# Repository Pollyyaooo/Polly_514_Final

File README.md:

# EmoTrace
#### MSTI TECHIN 514 Final Project           
#### 01/06/2026-03/06/2026

## Project Overview

This project investigates emotion sensing as a process of externalization rather than interpretation.
It measures physiological arousal through galvanic skin response (GSR) and expresses it using a
stepper-motor-driven physical needle display.

Instead of identifying discrete emotions or presenting numerical readouts, the system focuses on
how affective states unfold over time. Changes in arousal are rendered as continuous physical
motion, allowing inertia, gradual transitions, and recovery to remain visible rather than being
collapsed into instantaneous values.

The project is composed of two physically separated devices: a sensing device and a display device,
connected wirelessly via BLE. The sensing device captures and processes physiological signals, while
the display device externalizes these signals as a slow, glanceable, and non-intrusive physical
artifact. Through this separation, the project explores how emotional states can be felt,
noticed, and reflected upon, without being classified or explained away.

## System Architecture

**Sensing Device**
- Captures electrodermal activity via finger electrodes and a GSR sensor module
- Performs basic digital signal processing (filtering, baseline normalization)
- Transmits a continuous arousal indicator via BLE

**Display Device**
- Receives arousal data wirelessly
- Drives a stepper-motor-based gauge needle as the primary expressive output
- Provides minimal user input and status indication
- Is implemented on a custom-designed PCB

## Battery Estimation

### Display Device
Spreadsheet link:  
https://1drv.ms/x/c/3520740a59bca320/IQBtffllcoQcSJlxG03brPWNAZ11j2MDRlCTxOjXR5vgqAk?e=tpQcXu

### Sensing Device
Spreadsheet link:  
https://1drv.ms/x/c/3520740a59bca320/IQDMDjtJkVfMQYsOUzpoie-YAZGBVunHImL63yKkG8l4-dY?e=yHCJq8

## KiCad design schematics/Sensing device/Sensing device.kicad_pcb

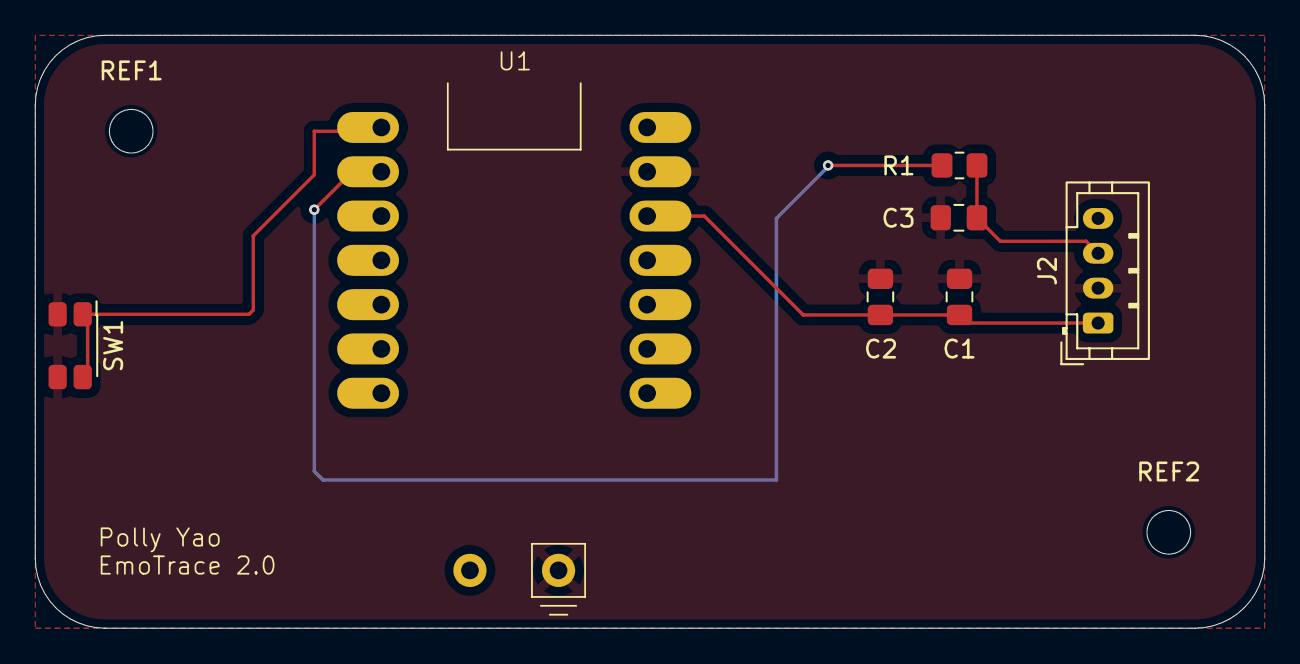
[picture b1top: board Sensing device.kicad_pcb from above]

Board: 2 copper layers, 70.5 x 34.0 mm, 9 parts (0 on the bottom side), 5 nets.

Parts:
C1: 10uF; C_0805_2012Metric_Pad1.18x1.45mm_HandSolder
C2, C3: 0.1uF; C_0805_2012Metric_Pad1.18x1.45mm_HandSolder
J2: Grove_GSR; JST_PH_B4B-PH-K_1x04_P2.00mm_Vertical
R1: 220Ω; R_0805_2012Metric_Pad1.20x1.40mm_HandSolder
REF1, REF2: MountingHole_2.5mm
SW1: SW_Push; SW_SPST_EVQP7A
U1: XIAO ESP32C3; XIAO_ESP32

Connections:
+3V3: C1.1, C2.1, J2.1, U1.12 (3V3)
/CAL_BTN: SW1.1, U1.1 (GPIO1_A0_D0)
/GSR_SIG: R1.2, U1.2 (GPIO2_A1_D1)
GND: C1.2, C2.2, C3.1, J2.2, SW1.2, U1.13 (GND), U1.16 (-BATT)
unnamed: C3.2, J2.3, R1.1

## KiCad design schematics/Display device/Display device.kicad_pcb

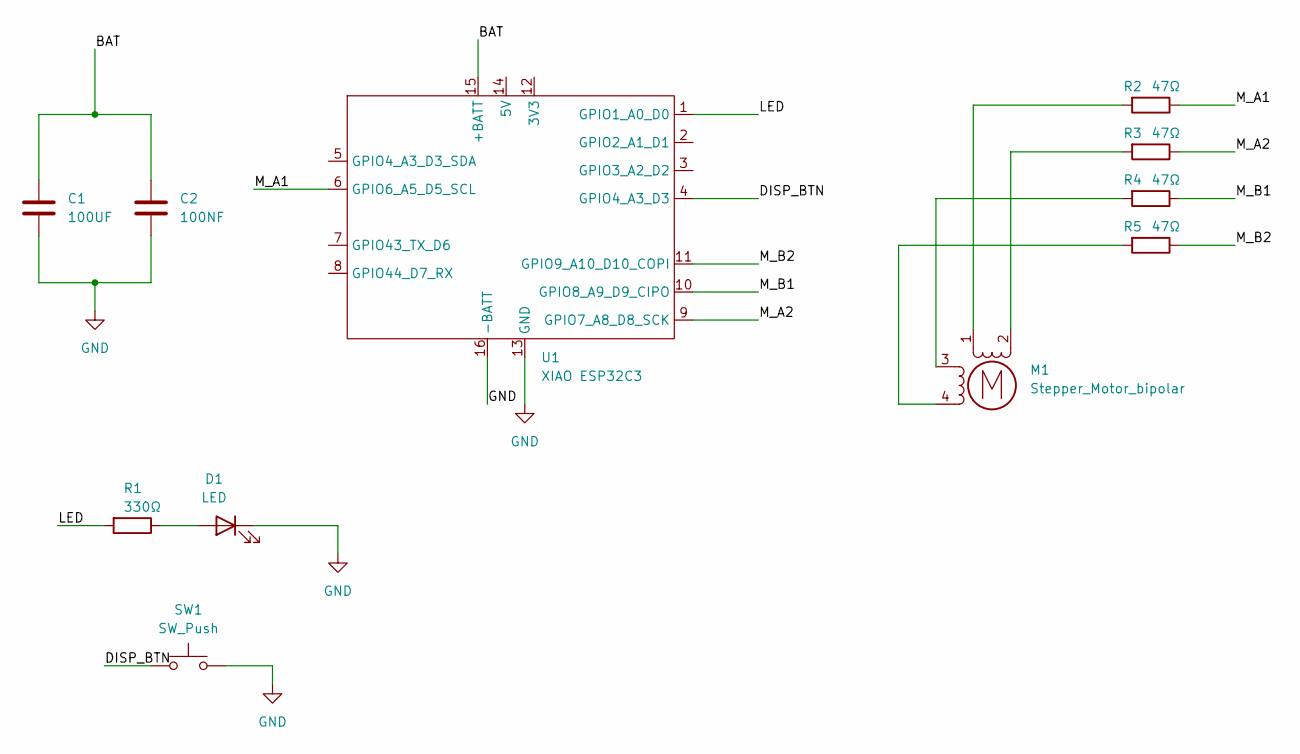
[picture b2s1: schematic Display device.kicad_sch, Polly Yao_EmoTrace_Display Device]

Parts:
C1: 100UF; C_0805_2012Metric_Pad1.18x1.45mm_HandSolder
C2: 100NF; C_0805_2012Metric_Pad1.18x1.45mm_HandSolder
D1: LED; LED_0805_2012Metric_Pad1.15x1.40mm_HandSolder
M1: Stepper_Motor_bipolar; x27_stepper_two_holes
R1: 330Ω; R_0805_2012Metric_Pad1.20x1.40mm_HandSolder
R2, R3, R4, R5: 47Ω; R_0805_2012Metric_Pad1.20x1.40mm_HandSolder
SW1: SW_Push; SW_SPST_EVQP7A
U1: XIAO ESP32C3; XIAO_ESP32

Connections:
/BAT: C1.1, C2.1, U1.15 (+BATT)
/DISP_BTN: SW1.1, U1.4 (GPIO4_A3_D3)
/LED: R1.2, U1.1 (GPIO1_A0_D0)
/M_A1: R2.1, U1.6 (GPIO6_A5_D5_SCL)
/M_A2: R3.1, U1.9 (GPIO7_A8_D8_SCK)
/M_B1: R4.1, U1.10 (GPIO8_A9_D9_CIPO)
/M_B2: R5.1, U1.11 (GPIO9_A10_D10_COPI)
GND: C1.2, C2.2, D1.1 (K), SW1.2, U1.13 (GND), U1.16 (-BATT)
unnamed: D1.2 (A), R1.1
unnamed: M1.2 (-), R3.2
unnamed: M1.1, R2.2
unnamed: M1.3, R4.2
unnamed: M1.4, R5.2

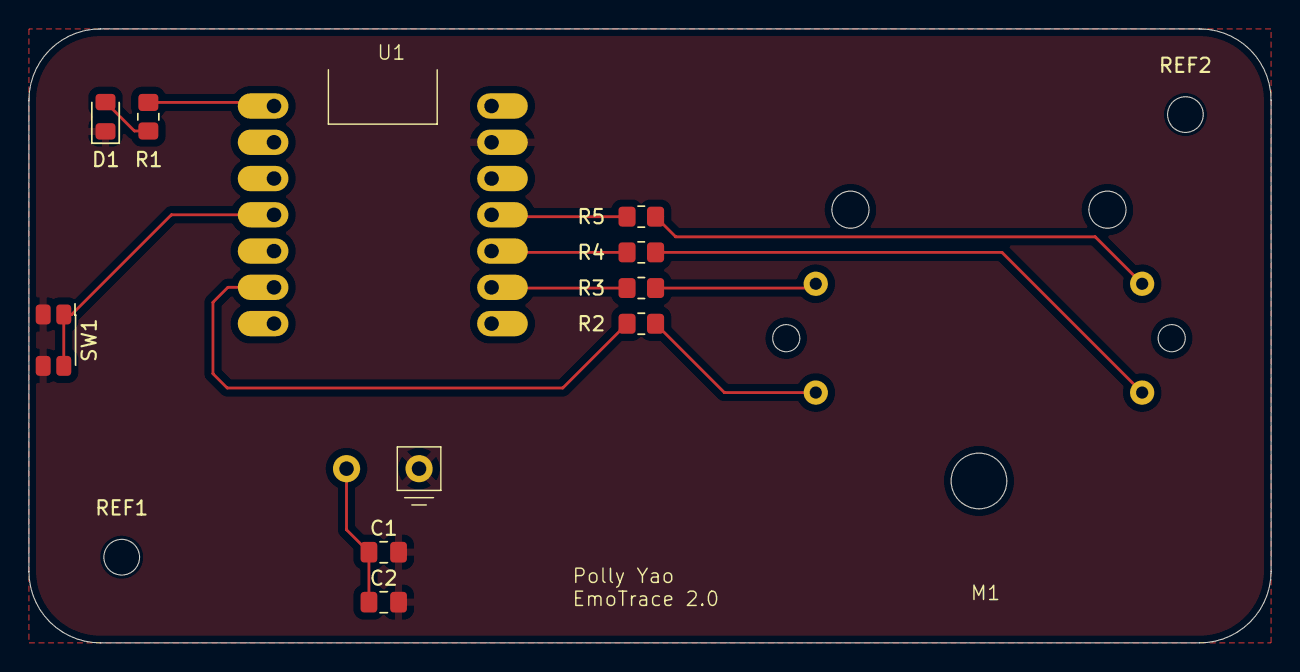
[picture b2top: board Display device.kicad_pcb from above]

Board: 2 copper layers, 87.0 x 43.0 mm, 13 parts (0 on the bottom side), 13 nets.

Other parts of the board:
REF1, REF2: MountingHole_2.5mm

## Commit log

2026-01-20 overview add
2026-01-20 images file add
2026-01-20 slides
2026-01-20 communication
2026-01-20 description
2026-01-20 communication add
2026-01-26 schematic add
2026-01-26 readme rewrite
2026-01-26 update sensing device
2026-01-27 update display device
2026-01-27 device
2026-02-02 kicad update
2026-02-04 update code
2026-02-08 datasheet update
2026-02-27 sche update
2026-03-01 code name update
2026-03-07 sensing update
